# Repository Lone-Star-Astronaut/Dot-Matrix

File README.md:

LED Dot-Matrix

This project is created to use the MAX7219 IC to drive LED 8x8 matrices to display scrolling text messages.
An Arduino UNO is used to communicate to the MAX7219 using a SPI interface. 

This project is still a work in progress. PCB layout and 3D printed enclosure files will be included as part of the project.

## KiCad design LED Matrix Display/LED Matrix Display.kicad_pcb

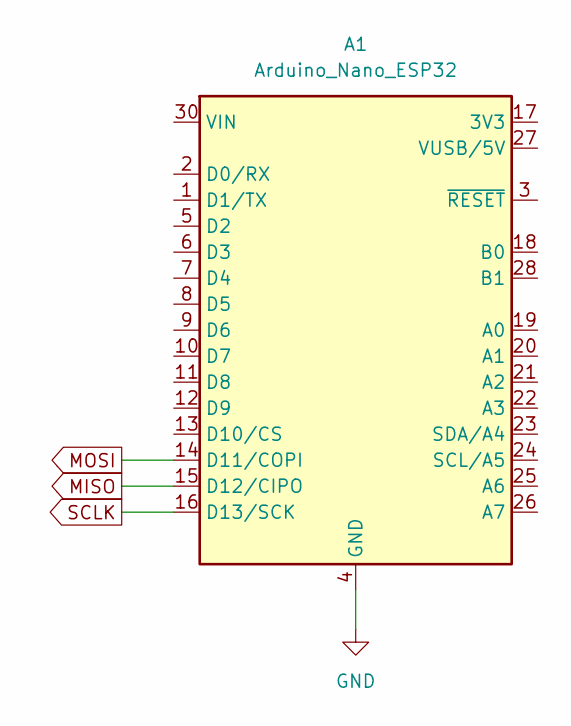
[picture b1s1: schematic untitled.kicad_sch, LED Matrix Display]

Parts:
A1: Arduino_Nano_ESP32; Arduino_Nano

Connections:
GND: A1.4 (GND), A1.29 (GND); also elsewhere on the board
MISO: A1.15 (D12/CIPO)
MOSI: A1.14 (D11/COPI); also elsewhere on the board
SCLK: A1.16 (D13/SCK); also elsewhere on the board

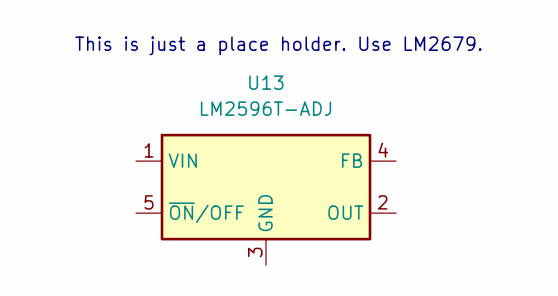
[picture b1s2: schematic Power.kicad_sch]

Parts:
U13: LM2596T-ADJ; TO-220-5_P3.4x3.7mm_StaggerOdd_Lead3.8mm_Vertical

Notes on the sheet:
This is just a place holder. Use LM2679.

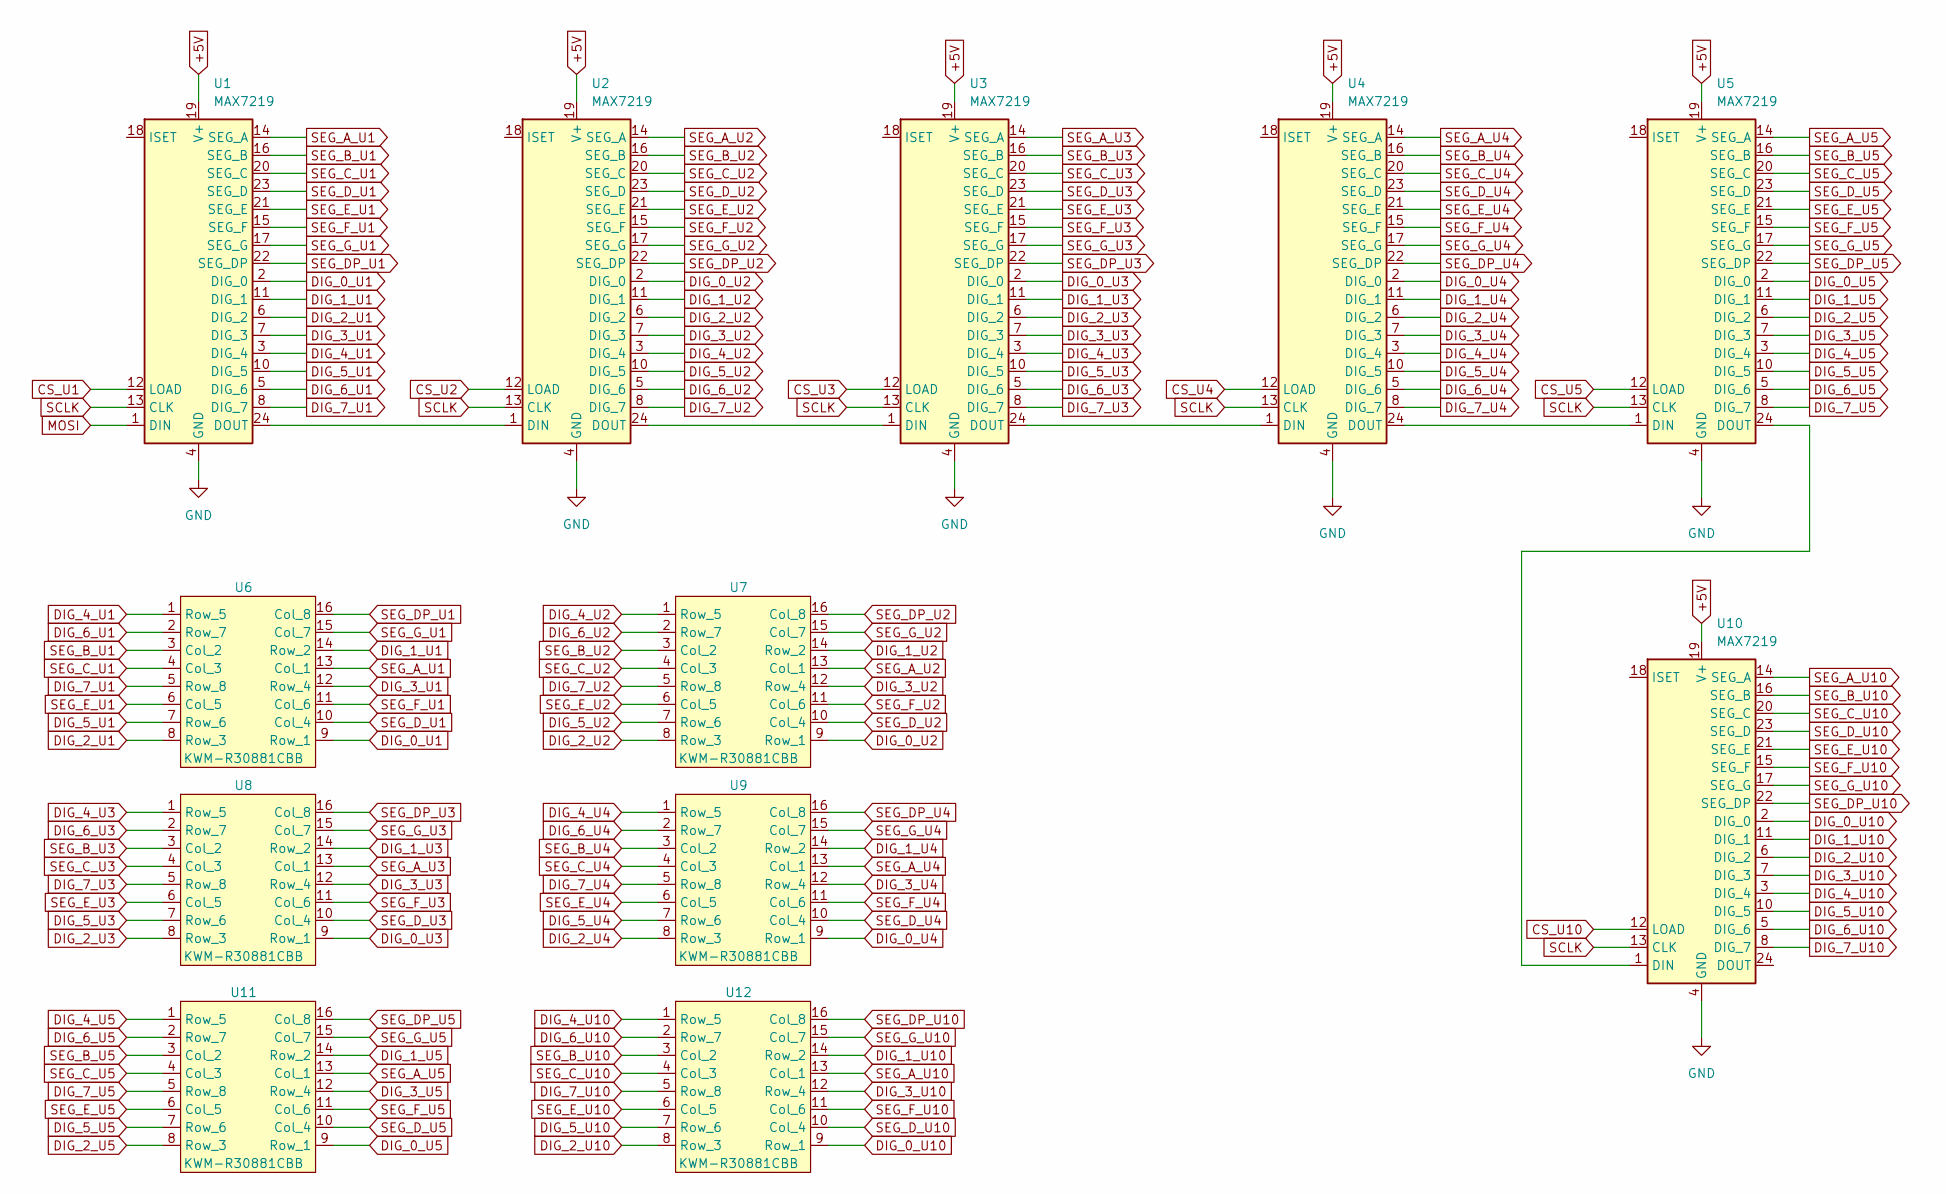
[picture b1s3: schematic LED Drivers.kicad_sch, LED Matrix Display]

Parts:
U1, U2, U3, U4, U5, U10: MAX7219; SOIC-24W_7.5x15.4mm_P1.27mm
U6, U7, U8, U9, U11, U12: KWM-R30881CBB

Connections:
+5V: U1.19 (V+), U2.19 (V+), U3.19 (V+), U4.19 (V+), U5.19 (V+), U10.19 (V+)
CS_U1: U1.12 (LOAD)
CS_U2: U2.12 (LOAD)
CS_U3: U3.12 (LOAD)
CS_U4: U4.12 (LOAD)
CS_U5: U5.12 (LOAD)
CS_U10: U10.12 (LOAD)
DIG_0_U1: U1.2 (DIG_0), U6.9 (Row_1)
DIG_0_U2: U2.2 (DIG_0), U7.9 (Row_1)
DIG_0_U3: U3.2 (DIG_0), U8.9 (Row_1)
DIG_0_U4: U4.2 (DIG_0), U9.9 (Row_1)
DIG_0_U5: U5.2 (DIG_0), U11.9 (Row_1)
DIG_0_U10: U10.2 (DIG_0), U12.9 (Row_1)
DIG_1_U1: U1.11 (DIG_1), U6.14 (Row_2)
DIG_1_U2: U2.11 (DIG_1), U7.14 (Row_2)
DIG_1_U3: U3.11 (DIG_1), U8.14 (Row_2)
DIG_1_U4: U4.11 (DIG_1), U9.14 (Row_2)
DIG_1_U5: U5.11 (DIG_1), U11.14 (Row_2)
DIG_1_U10: U10.11 (DIG_1), U12.14 (Row_2)
DIG_2_U1: U1.6 (DIG_2), U6.8 (Row_3)
DIG_2_U2: U2.6 (DIG_2), U7.8 (Row_3)
DIG_2_U3: U3.6 (DIG_2), U8.8 (Row_3)
DIG_2_U4: U4.6 (DIG_2), U9.8 (Row_3)
DIG_2_U5: U5.6 (DIG_2), U11.8 (Row_3)
DIG_2_U10: U10.6 (DIG_2), U12.8 (Row_3)
DIG_3_U1: U1.7 (DIG_3), U6.12 (Row_4)
DIG_3_U2: U2.7 (DIG_3), U7.12 (Row_4)
DIG_3_U3: U3.7 (DIG_3), U8.12 (Row_4)
DIG_3_U4: U4.7 (DIG_3), U9.12 (Row_4)
DIG_3_U5: U5.7 (DIG_3), U11.12 (Row_4)
DIG_3_U10: U10.7 (DIG_3), U12.12 (Row_4)
DIG_4_U1: U1.3 (DIG_4), U6.1 (Row_5)
DIG_4_U2: U2.3 (DIG_4), U7.1 (Row_5)
DIG_4_U3: U3.3 (DIG_4), U8.1 (Row_5)
DIG_4_U4: U4.3 (DIG_4), U9.1 (Row_5)
DIG_4_U5: U5.3 (DIG_4), U11.1 (Row_5)
DIG_4_U10: U10.3 (DIG_4), U12.1 (Row_5)
DIG_5_U1: U1.10 (DIG_5), U6.7 (Row_6)
DIG_5_U2: U2.10 (DIG_5), U7.7 (Row_6)
DIG_5_U3: U3.10 (DIG_5), U8.7 (Row_6)
DIG_5_U4: U4.10 (DIG_5), U9.7 (Row_6)
DIG_5_U5: U5.10 (DIG_5), U11.7 (Row_6)
DIG_5_U10: U10.10 (DIG_5), U12.7 (Row_6)
DIG_6_U1: U1.5 (DIG_6), U6.2 (Row_7)
DIG_6_U2: U2.5 (DIG_6), U7.2 (Row_7)
DIG_6_U3: U3.5 (DIG_6), U8.2 (Row_7)
DIG_6_U4: U4.5 (DIG_6), U9.2 (Row_7)
DIG_6_U5: U5.5 (DIG_6), U11.2 (Row_7)
DIG_6_U10: U10.5 (DIG_6), U12.2 (Row_7)
DIG_7_U1: U1.8 (DIG_7), U6.5 (Row_8)
DIG_7_U2: U2.8 (DIG_7), U7.5 (Row_8)
DIG_7_U3: U3.8 (DIG_7), U8.5 (Row_8)
DIG_7_U4: U4.8 (DIG_7), U9.5 (Row_8)
DIG_7_U5: U5.8 (DIG_7), U11.5 (Row_8)
DIG_7_U10: U10.8 (DIG_7), U12.5 (Row_8)
GND: U1.4 (GND), U1.9 (GND), U2.4 (GND), U2.9 (GND), U3.4 (GND), U3.9 (GND), U4.4 (GND), U4.9 (GND), U5.4 (GND), U5.9 (GND), U10.4 (GND), U10.9 (GND); also elsewhere on the board
MOSI: U1.1 (DIN); also elsewhere on the board
unnamed: U1.24 (DOUT), U2.1 (DIN)
unnamed: U2.24 (DOUT), U3.1 (DIN)
unnamed: U3.24 (DOUT), U4.1 (DIN)
unnamed: U4.24 (DOUT), U5.1 (DIN)
unnamed: U5.24 (DOUT), U10.1 (DIN)
SCLK: U1.13 (CLK), U2.13 (CLK), U3.13 (CLK), U4.13 (CLK), U5.13 (CLK), U10.13 (CLK); also elsewhere on the board
SEG_A_U1: U1.14 (SEG_A), U6.13 (Col_1)
SEG_A_U2: U2.14 (SEG_A), U7.13 (Col_1)
SEG_A_U3: U3.14 (SEG_A), U8.13 (Col_1)
SEG_A_U4: U4.14 (SEG_A), U9.13 (Col_1)
SEG_A_U5: U5.14 (SEG_A), U11.13 (Col_1)
SEG_A_U10: U10.14 (SEG_A), U12.13 (Col_1)
SEG_B_U1: U1.16 (SEG_B), U6.3 (Col_2)
SEG_B_U2: U2.16 (SEG_B), U7.3 (Col_2)
SEG_B_U3: U3.16 (SEG_B), U8.3 (Col_2)
SEG_B_U4: U4.16 (SEG_B), U9.3 (Col_2)
SEG_B_U5: U5.16 (SEG_B), U11.3 (Col_2)
SEG_B_U10: U10.16 (SEG_B), U12.3 (Col_2)
SEG_C_U1: U1.20 (SEG_C), U6.4 (Col_3)
SEG_C_U2: U2.20 (SEG_C), U7.4 (Col_3)
SEG_C_U3: U3.20 (SEG_C), U8.4 (Col_3)
SEG_C_U4: U4.20 (SEG_C), U9.4 (Col_3)
SEG_C_U5: U5.20 (SEG_C), U11.4 (Col_3)
SEG_C_U10: U10.20 (SEG_C), U12.4 (Col_3)
SEG_DP_U1: U1.22 (SEG_DP), U6.16 (Col_8)
SEG_DP_U2: U2.22 (SEG_DP), U7.16 (Col_8)
SEG_DP_U3: U3.22 (SEG_DP), U8.16 (Col_8)
SEG_DP_U4: U4.22 (SEG_DP), U9.16 (Col_8)
SEG_DP_U5: U5.22 (SEG_DP), U11.16 (Col_8)
SEG_DP_U10: U10.22 (SEG_DP), U12.16 (Col_8)
SEG_D_U1: U1.23 (SEG_D), U6.10 (Col_4)
SEG_D_U2: U2.23 (SEG_D), U7.10 (Col_4)
SEG_D_U3: U3.23 (SEG_D), U8.10 (Col_4)
SEG_D_U4: U4.23 (SEG_D), U9.10 (Col_4)
SEG_D_U5: U5.23 (SEG_D), U11.10 (Col_4)
SEG_D_U10: U10.23 (SEG_D), U12.10 (Col_4)
SEG_E_U1: U1.21 (SEG_E), U6.6 (Col_5)
SEG_E_U2: U2.21 (SEG_E), U7.6 (Col_5)
SEG_E_U3: U3.21 (SEG_E), U8.6 (Col_5)
SEG_E_U4: U4.21 (SEG_E), U9.6 (Col_5)
SEG_E_U5: U5.21 (SEG_E), U11.6 (Col_5)
SEG_E_U10: U10.21 (SEG_E), U12.6 (Col_5)
SEG_F_U1: U1.15 (SEG_F), U6.11 (Col_6)
SEG_F_U2: U2.15 (SEG_F), U7.11 (Col_6)
SEG_F_U3: U3.15 (SEG_F), U8.11 (Col_6)
SEG_F_U4: U4.15 (SEG_F), U9.11 (Col_6)
SEG_F_U5: U5.15 (SEG_F), U11.11 (Col_6)
SEG_F_U10: U10.15 (SEG_F), U12.11 (Col_6)
SEG_G_U1: U1.17 (SEG_G), U6.15 (Col_7)
SEG_G_U2: U2.17 (SEG_G), U7.15 (Col_7)
SEG_G_U3: U3.17 (SEG_G), U8.15 (Col_7)
SEG_G_U4: U4.17 (SEG_G), U9.15 (Col_7)
SEG_G_U5: U5.17 (SEG_G), U11.15 (Col_7)
SEG_G_U10: U10.17 (SEG_G), U12.15 (Col_7)

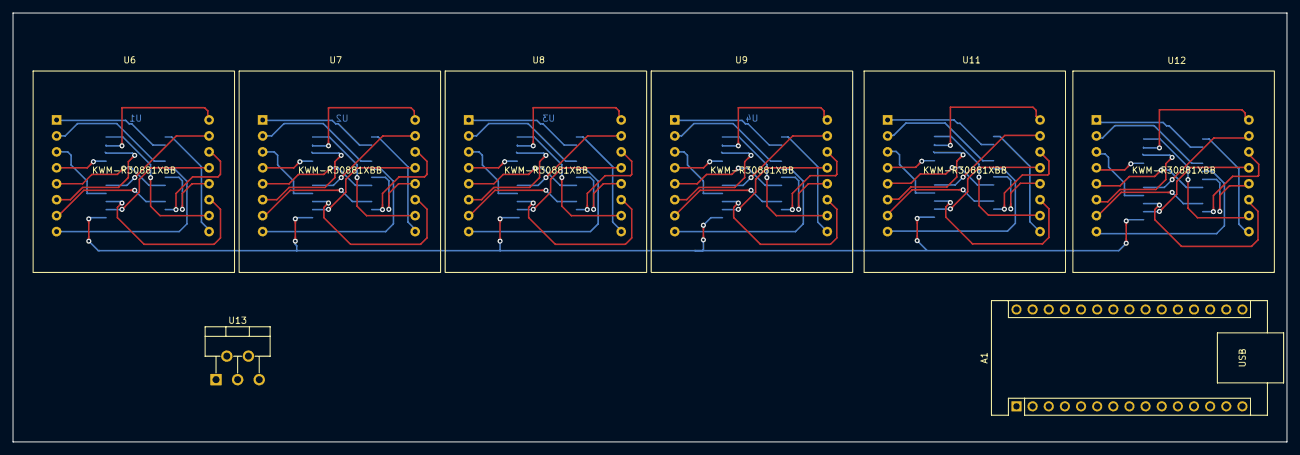
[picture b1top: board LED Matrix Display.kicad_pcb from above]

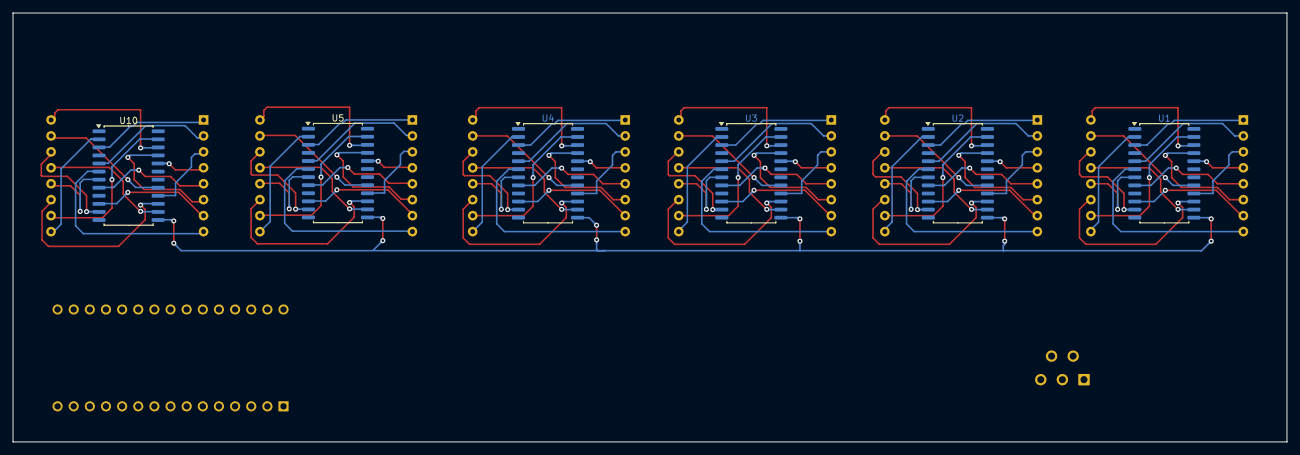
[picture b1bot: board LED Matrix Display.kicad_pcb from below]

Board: 2 copper layers, 200.5 x 67.5 mm, 14 parts (6 on the bottom side), 105 nets.

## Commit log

2024-11-26 Add files via upload
    Uploading PCB design files.
2025-02-08 Serial communication implemented
    Added some code to enable serial communication over USB.
2025-02-10 Add files via upload
    Actual PCB/SCH files. Others were empty.
2025-02-11 Added more ASCII characters
    Added more ASCII characters
2025-03-06 SCH and PCB updates
    Added updates to SCH and made progress on layout.
2025-03-06 Display Test
    Quick video of working scrolling text.
